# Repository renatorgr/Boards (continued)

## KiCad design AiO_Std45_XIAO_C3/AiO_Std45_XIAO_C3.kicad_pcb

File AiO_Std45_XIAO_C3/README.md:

# XIAO ESP32C3 adapter for the AiO v4.5 Standard (GPS2 socket → Serial2)

A small board (40.0 × 52.6 mm overall, 2 layers, cut away where the Bynav / UM982 module goes) that plugs into the **second GPS socket (GPS2, "F9P RelPosNED")** of the AiO v4.5 Standard, in place of a second simpleRTK2B, and connects a **Seeed XIAO ESP32C3** (or **ESP32S3**) to the **Teensy's Serial2** (pins 7 and 8). The XIAO plugs into two female headers on the adapter.

## Connections

| Socket pin | On the AiO v4.5 Standard | On the adapter |
|---|---|---|
| P8 pin 1 | Teensy pin 7 (RX2) | R1 1 kΩ → D6 (TX) |
| P8 pin 2 | Teensy pin 8 (TX2) | R2 1 kΩ → D7 (RX) |
| P8 pin 3 | pin 1 of H6 (GPS1 socket, dual F9P only) | not connected |
| P7 pin 4 | 5 V (5V1, K7805M 1 A regulator) | D1 (Schottky) → XIAO 5V pin + C1 22 µF |
| P7 pins 2, 3 | GND | GND |
| P7 pin 7 | 3.3 V of the Teensy (IOREF) | **not connected** |
| P7 pins 1, 5, 6, 8 | — | not connected |
| H14 pins 1–6 | — (A0–A5 of the socket, no connections) | not connected: they hold the adapter |

- XIAO ESP32C3: D6 = GPIO21 (TX), D7 = GPIO20 (RX).
- XIAO ESP32S3: D6 = GPIO43 (TX), D7 = GPIO44 (RX).

The positions of the 17 pins were copied from the official AiO v4.5 Standard PCB file (EasyEDA, 2024-02-05) and the nets were checked against its schematic (2024-03-27): 0.000 mm difference.

## Why 5 V and not 3.3 V

- On the Standard, the 3.3 V of the GPS2 socket (P7 pin 7, IOREF) is the Teensy's own 3.3 V output.
- PJRC recommends at most 250 mA from it for external use, and the board already uses it (BNO085, CAN, LEDs, ...). The ESP32's WiFi transmit peaks can go over that.
- The Micro is different: its GPS2 socket has its own 1 A 3.3 V regulator, so the Micro adapter uses 3.3 V.
- This adapter takes the 5 V of the socket (P7 pin 4) through a Schottky diode (D1) into the XIAO's 5V pin, and the XIAO makes its own 3.3 V. Seeed asks for this diode when the 5V pin is fed from outside.
- With D1, the XIAO's USB-C can be plugged in with the adapter on the board: D1 keeps the USB 5 V out of the AiO's 5 V.
- R1 and R2 are 1 kΩ (the Micro adapter too, from its v1.2). If the XIAO is on USB with the AiO switched off, its TX pin feeds the unpowered Teensy through R1; 1 kΩ keeps that current to about 3 mA. At 460800 baud, 1 kΩ makes no difference.

## Shape

- It plugs into P7 (power), P8 pins 1–3 (Serial2) and H14 (6 pins, only to hold it).
- The XIAO sits on the H14 / P8 side of the socket (towards the ADS1115), with its USB-C on the left edge.
- A strip along P7 carries the 5 V. Everything to the right of the XIAO and below that strip is cut away: from 4.0 mm to the right of P7 pin 1 and from 4.6 mm below the P7 row. The Bynav / UM982 module (and the U16 MP1584) can sit under that area.
- A leg goes down to P8 and stays at least 1.5 mm away from the UM982 board drawn on the official PCB (part GPS_UM982EB, socket H20), which covers P8 pins 5–8 and H7.
- P8 and P7 alone would let the adapter go in turned 180°. With H14 it cannot: turned around, its H14 pins land between the holes of H7.
- The outline stays inside the drawing of the GPS2 module on the Standard's silkscreen.

## Files

- `AiO_Std45_XIAO_C3.kicad_pro / .kicad_sch / .kicad_pcb`: KiCad 7 project (schematic + PCB), with its own libraries (`AiO_XIAO_Adapter.pretty`, `AiO_XIAO_Adapter.kicad_sym`).
- `fabrication_JLCPCB/Gerber_AiO_Std45_XIAO_C3.zip`: Gerbers + drill file, ready for JLCPCB.
- `fabrication_JLCPCB/BOM_…csv` and `CPL_…csv`: for JLCPCB's assembly (R1, R2, C1, D1 and the XIAO sockets J4, J5 on the top side, the pin headers J1, J2 and J3 on the bottom side).
- `fabrication_JLCPCB/BOM_…_top_only.csv` and `CPL_…_top_only.csv`: the same without J1, J2 and J3, for an assembly on the top side only.
- `documentation/`: the schematic as a PDF (`adapter_schematic.pdf`), views of the board (`adapter_PCB.png`) and its position on the Standard (`GPS2_socket_view.png`).

## Opening it in EasyEDA

EasyEDA Pro: **File → Import → KiCad**, then choose the project folder (or the .zip). It imports the schematic and the PCB.
EasyEDA is not needed to order the board: the Gerber zip goes straight to JLCPCB.

## Ordering (JLCPCB)

- Gerber: `Gerber_AiO_Std45_XIAO_C3.zip`. 2 layers, 1.6 mm, any colour. The default settings are fine (minimum track 0.3 mm, minimum hole 0.3 mm).
- Assembly: BOM + CPL. JLCPCB solders everything except the XIAO:
  - R1, R2, C1 and D1: SMD parts on the top side;
  - the pin headers J1, J2 and J3: through-hole parts on the **bottom** side, with the long pins pointing down (away from the board). The CPL already gives them on the bottom layer, at the centre of each header;
  - the two female headers J4 and J5 for the XIAO: through-hole parts on the **top** side.
- Through-hole assembly costs a little more than SMD only.
- There are parts on both sides, so choose **Standard PCBA** with assembly on **both sides**. With Economic PCBA or top side only, JLCPCB leaves out J1, J2 and J3 (they are on the bottom) and stops with "Coordinate file missing data for: J1, J2, J3".
- Cheaper alternative: Economic PCBA, top side only, with `BOM_…_top_only.csv` and `CPL_…_top_only.csv` (the same files without J1, J2 and J3), and solder J1, J2 and J3 by hand.
- In JLCPCB's placement preview, check:
  - J1, J2 and J3 on the bottom side, over the rows of holes marked "P8", "P7" and "H14";
  - J4 and J5 on the top side, over the two rows of 7 holes of the XIAO;
  - D1: its band (cathode) on the C1 side, as on the silkscreen.

| Ref. | Part | LCSC |
|---|---|---|
| R1, R2 | 1 kΩ 1 % 0805 | C17513 |
| C1 | 22 µF 0805 X5R 25 V | C45783 |
| D1 | B5819W Schottky 40 V 1 A, SOD-123 | C8598 |
| J1 | 1x03 male header, 2.54 mm, XFCN PZ254V-11-03P | C2937625 |
| J2 | 1x08 male header, 2.54 mm, XFCN PZ254V-11-08P | C492407 |
| J3 | 1x06 male header, 2.54 mm, XFCN PZ254V-11-06P | C492405 |
| J4, J5 | 1x07 female header, 2.54 mm, 8.5 mm high, HCTL PM254-1-07-Z-8.5 | C2897370 |
| U1 | Seeed XIAO ESP32C3 or ESP32S3, plugged into J4 / J5 | (not assembled) |

The headers have 6.1 mm mating pins and a 2.5 mm insulator, like the ones on the AiO board itself. Without assembly, J1, J2 and J3 can be cut from one ordinary 1x40 strip of 2.54 mm male headers.

## Assembly

1. Only if the board did not come assembled: R1, R2, C1 and D1 (D1: the band towards C1), then the headers.
2. **The male headers go underneath**, with the long pins pointing down. When soldering them by hand, to get them well aligned: push them into the Standard's P8, P7 and H14, lay the adapter on top and solder them from above.
   - J1 goes into **P8 pins 1 to 3**: the three holes at the end of P8 closest to the ADS1115 module.
   - J2 goes into P7 (all 8 pins) and J3 into H14 (all 6 pins).
3. **XIAO:** solder the two 1x7 male headers that come with it **underneath the XIAO**, long pins pointing down. To keep them straight, push them into J4 and J5 first, lay the XIAO on top and solder from above.
4. **Plug the XIAO into J4 and J5 with its USB-C at the "USB-C" mark** (left edge, ADS1115 side). The two rows have 7 pins each, so the XIAO also goes in turned 180°: that way the 5 V goes into D6 (a 3.3 V pin) and the XIAO is damaged. Check the USB-C mark before powering the AiO.
5. Orientation of the adapter: the square pads are pin 1, and the silkscreen says "P8", "P7" and "H14" next to the header that goes into each one. The H14 header stops it going in turned around.

## Cautions

- With the adapter in place, the GPS2 socket cannot hold a second F9P (dual F9P).
- The Bynav / UM982 module (H20) and the XIAO can be fitted at the same time. They use different serial ports (the module the GPS1 port, the XIAO Serial2), and both take their 5 V from the 1 A K7805M (5V1).
- Check that the antenna cables of the Bynav / UM982 module do not press on the adapter.
- If there is a standoff in the GPS2 mounting hole next to the ADS1115 (left there for a simpleRTK2B), take it out: it would push on the adapter's leg.
- The XIAO's USB-C can be used with the adapter on the board (see "Why 5 V"): the plug goes in from the left, over the ADS1115 side. The XIAO can also be unplugged to program it, or programmed over WiFi (OTA) after the first time.
- On the sockets the XIAO sits about 11 mm higher than soldered flat (8.5 mm socket + 2.5 mm of the male header). Check that the box lid closes.
- Tractor vibration: hold the XIAO in its sockets, for example with a cable tie around the XIAO and the adapter, or a dot of neutral-cure silicone at the corners (not on the U.FL connector or the buttons).
- In a metal box, use an external WiFi antenna on the XIAO's U.FL connector, taken out through the box.

## Firmware

- Teensy: firmware `v4.5_AiO_WEB`, Serial2 (pins 7 RX2 and 8 TX2) at **460800**. On its web page, Settings → "GPS2 port" must be on automatic (the default): the Teensy finds the XIAO by its hello.
- XIAO: the program `v4.5_XIAO_ESP32` that comes in the firmware zip (already compiled in `v4.5_XIAO_ESP32_bin`, for the C3 and the S3). It uses UART1 on D7 (RX) and D6 (TX) at 460800 and empties the receive FIFO at 64 bytes (`setRxFIFOFull(64)`).
- When it starts, the ESP32 writes a few boot lines at 115200 on D6: the Teensy receives garbage for half a second, and the firmware ignores it.
- The official firmware v26 (Firmware_Teensy_AiO-New-Dawn) uses this same link (Serial2) for its ESP32, also at 460800. See `docs/ESP32_BRIDGE_INTERFACE.md` in that repository.

## Checks done

- The schematic and the PCB have the same connections (netlist exported from the schematic = PCB connections).
- KiCad 7 DRC: 0 errors, 0 warnings, 0 unconnected items.
- The 17 header holes in the drill file match P8 pins 1–3, P7 and H14 of the official AiO v4.5 Standard PCB (AgOpenGPS-Official/Boards): 0.000 mm difference.
- The nets of P8, P7 and H14 checked against the official AiO v4.5 Standard schematic.
- The outline is at least 1.5 mm away from the UM982 board (GPS_UM982EB) drawn on the official PCB, and nothing of the adapter is right of the cut (4.0 mm right of P7 pin 1, 4.6 mm below the P7 row).
- The XIAO sockets J4 and J5 are on the XIAO pin positions of Seeed's official KiCad library (XIAO-ESP32-C3-DIP-SMD): 2 × 7 pins, 2.54 mm, rows 15.24 mm apart.
- J1, J2 and J3 are on the bottom side and J4, J5 on the top side, in the PCB and in the CPL. The holes are the same as in 1.1.
- Not yet made or tested on a real board.

## Versions

- **1.2** (19 Oct 2026): pin headers J1, J2 and J3 with LCSC codes in the BOM and the CPL (bottom side), so JLCPCB solders them too. The XIAO plugs into two 1x7 female headers (J4, J5, top side, also soldered by JLCPCB) instead of being soldered to the board.
- **1.1** (19 Oct 2026): XIAO moved to the H14 / P8 side, USB-C on the left edge; board cut away to the right of the XIAO so the Bynav / UM982 module can be fitted under that area.
- **1.0** (19 Oct 2026): first version (not made).

## Credits

- Design: renatorgr, with Claude (Anthropic), 2026.
- Pin positions and nets: official AiO v4.5 Standard board files (EasyEDA PCB 2024-02-05, schematic 2024-03-27), AgOpenGPS-Official/Boards.
- XIAO pin positions: Seeed Studio OPL KiCad library (XIAO-ESP32-C3-DIP-SMD). 0805 and SOD-123 footprints: KiCad standard library.

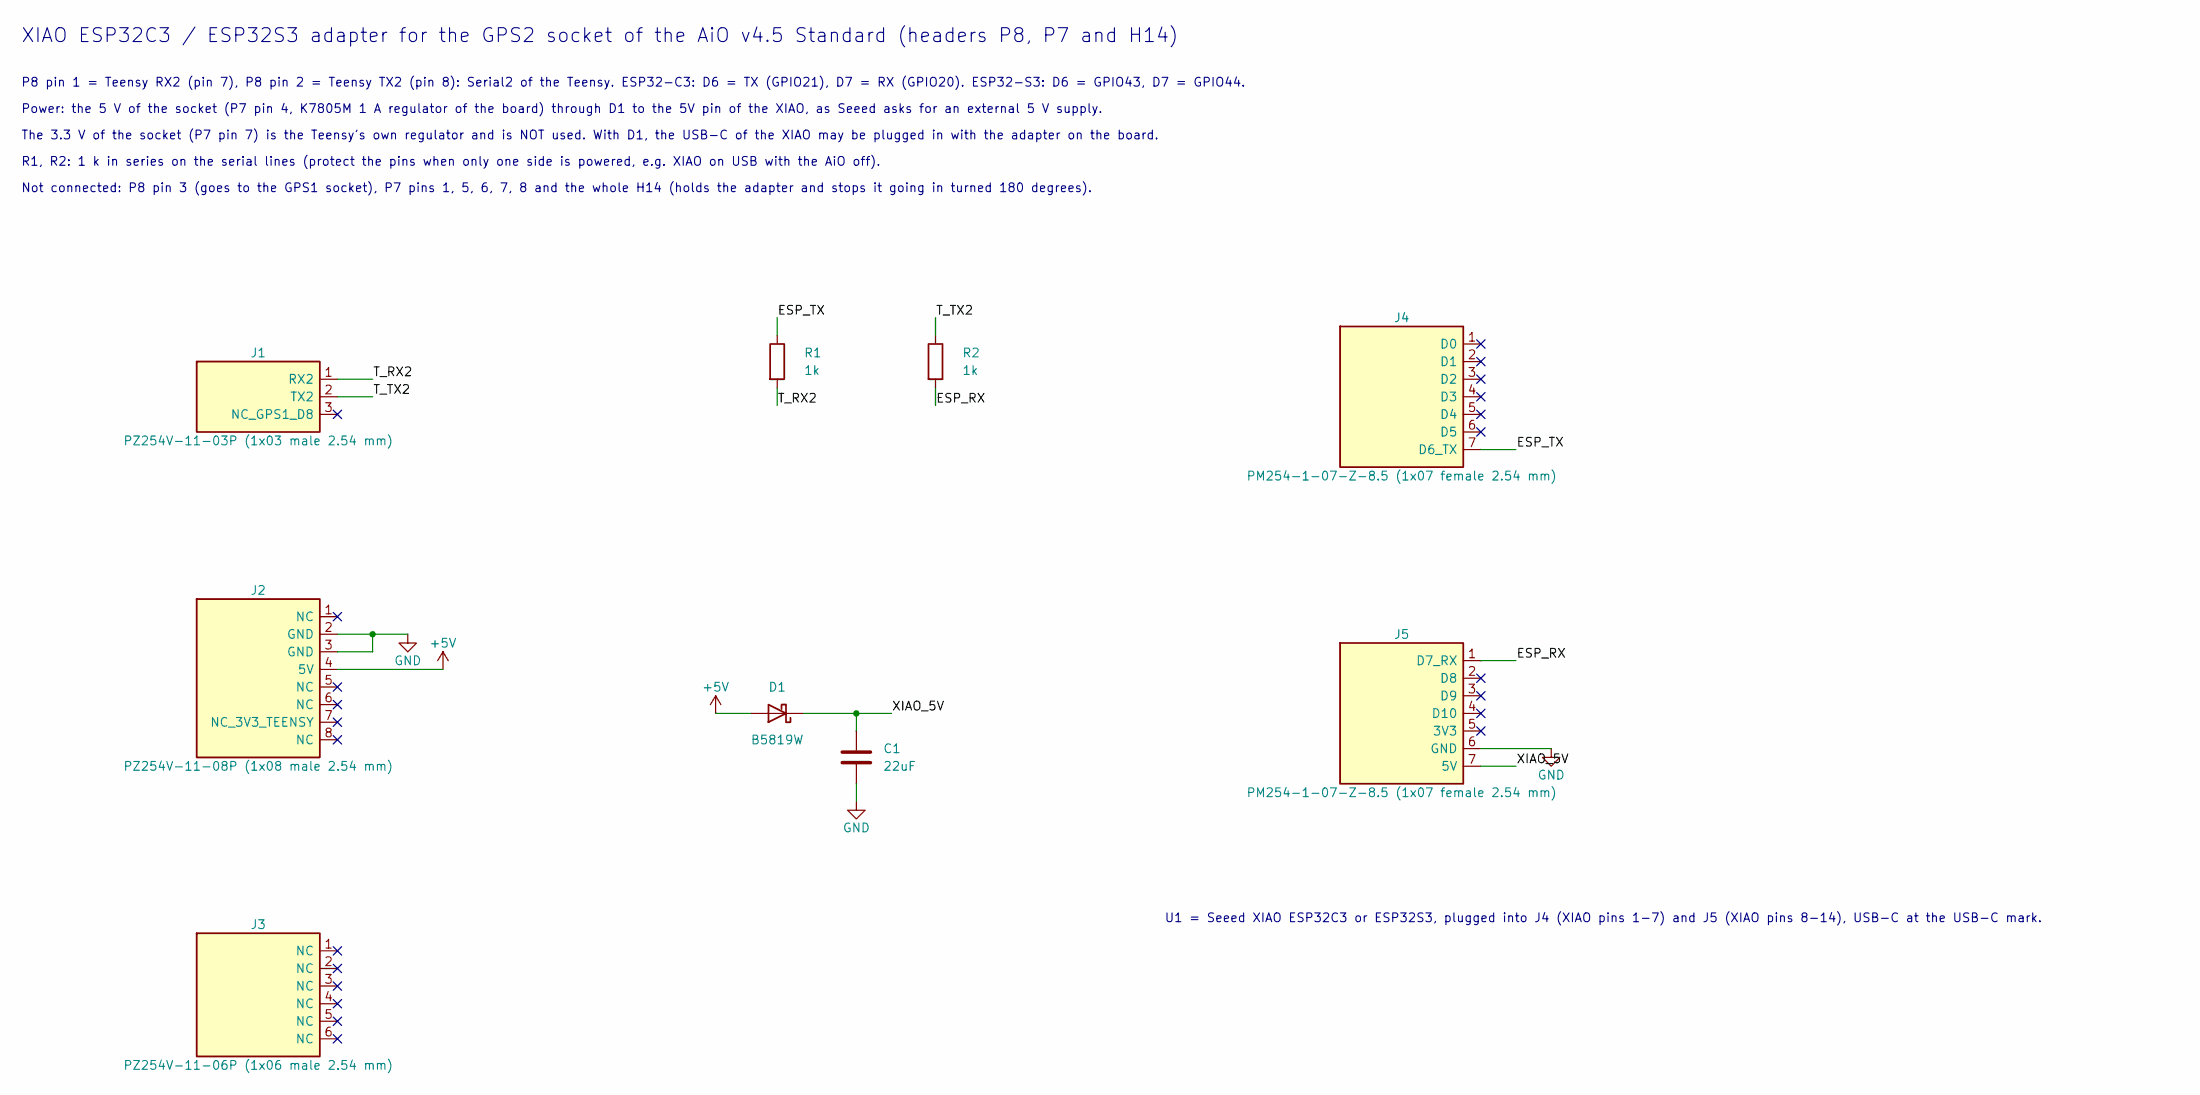
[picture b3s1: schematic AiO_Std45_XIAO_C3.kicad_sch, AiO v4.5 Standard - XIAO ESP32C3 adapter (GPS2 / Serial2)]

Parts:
C1: 22uF; C_0805_2012Metric; LCSC C45783
D1: B5819W; D_SOD-123; LCSC C8598
J1: PZ254V-11-03P (1x03 male 2.54 mm); Plug_1x03_P2.54mm_Bottom; LCSC C2937625
J2: PZ254V-11-08P (1x08 male 2.54 mm); Plug_1x08_P2.54mm_Bottom; LCSC C492407
J3: PZ254V-11-06P (1x06 male 2.54 mm); Plug_1x06_P2.54mm_Bottom; LCSC C492405
J4, J5: PM254-1-07-Z-8.5 (1x07 female 2.54 mm); Socket_1x07_P2.54mm_XIAO; LCSC C2897370
R1, R2: 1k; R_0805_2012Metric; LCSC C17513

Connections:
+5V: D1.2 (A), J2.4 (5V)
/ESP_RX: J5.1 (D7_RX), R2.2
/ESP_TX: J4.7 (D6_TX), R1.1
/T_RX2: J1.1 (RX2), R1.2
/T_TX2: J1.2 (TX2), R2.1
/XIAO_5V: C1.1, D1.1 (K), J5.7 (5V)
GND: C1.2, J2.2 (GND), J2.3 (GND), J5.6 (GND)

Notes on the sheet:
U1 = Seeed XIAO ESP32C3 or ESP32S3, plugged into J4 (XIAO pins 1-7) and J5 (XIAO pins 8-14), USB-C at the USB-C mark.
XIAO ESP32C3 / ESP32S3 adapter for the GPS2 socket of the AiO v4.5 Standard (headers P8, P7 and H14)
P8 pin 1 = Teensy RX2 (pin 7), P8 pin 2 = Teensy TX2 (pin 8): Serial2 of the Teensy. ESP32-C3: D6 = TX (GPIO21), D7 = RX (GPIO20). ESP32-S3: D6 = GPIO43, D7 = GPIO44.
Power: the 5 V of the socket (P7 pin 4, K7805M 1 A regulator of the board) through D1 to the 5V pin of the XIAO, as Seeed asks for an external 5 V supply.
The 3.3 V of the socket (P7 pin 7) is the Teensy's own regulator and is NOT used. With D1, the USB-C of the XIAO may be plugged in with the adapter on the board.
R1, R2: 1 k in series on the serial lines (protect the pins when only one side is powered, e.g. XIAO on USB with the AiO off).
Not connected: P8 pin 3 (goes to the GPS1 socket), P7 pins 1, 5, 6, 7, 8 and the whole H14 (holds the adapter and stops it going in turned 180 degrees).

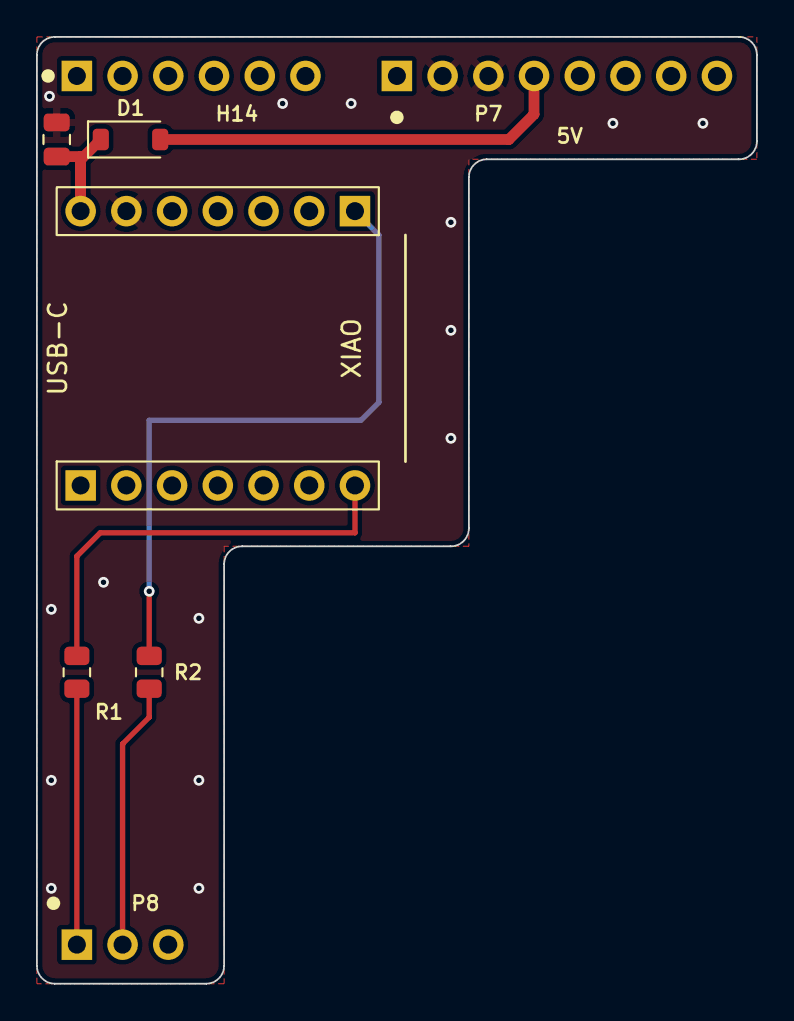
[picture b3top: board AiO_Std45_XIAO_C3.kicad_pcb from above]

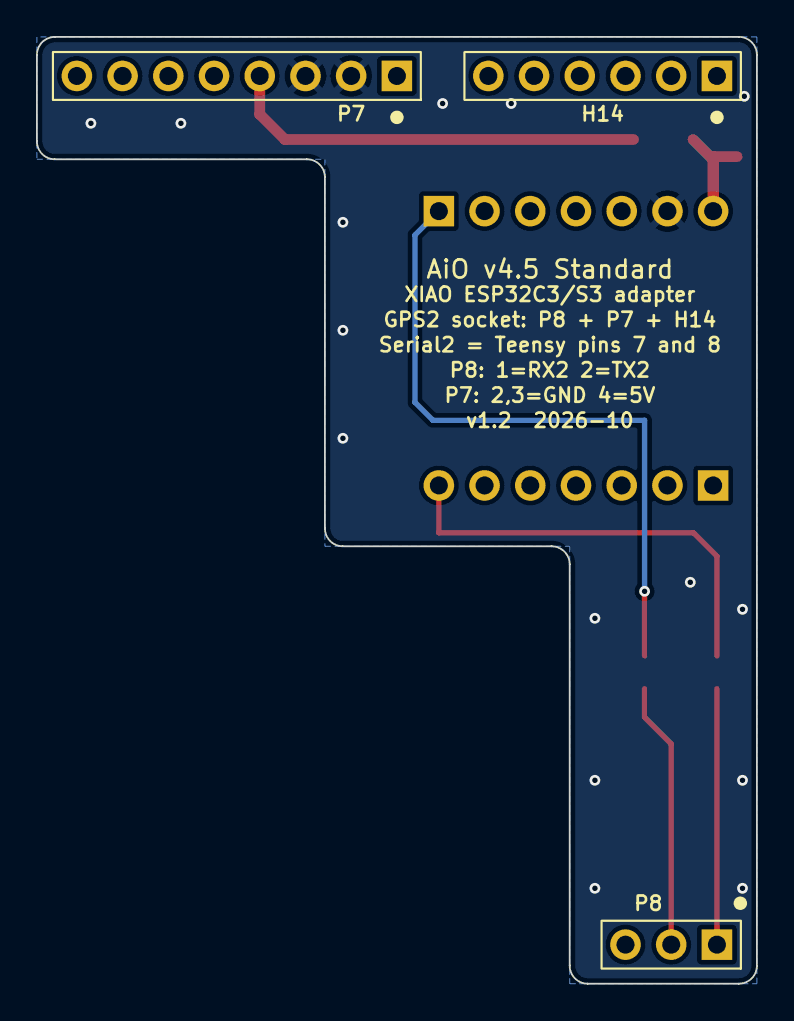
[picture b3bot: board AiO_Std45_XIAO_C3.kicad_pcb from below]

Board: 2 copper layers, 40.0 x 52.6 mm, 9 parts (3 on the bottom side), 7 nets.

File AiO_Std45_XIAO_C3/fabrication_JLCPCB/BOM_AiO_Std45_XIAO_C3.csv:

Comment,Designator,Footprint,LCSC Part #
1k 1% 0805,"R1,R2",R_0805_2012Metric,C17513
22uF 0805 X5R,C1,C_0805_2012Metric,C45783
B5819W Schottky 40V 1A,D1,D_SOD-123,C8598
Pin header 1x03 male 2.54mm PZ254V-11-03P (bottom side),J1,Plug_1x03_P2.54mm_Bottom,C2937625
Pin header 1x08 male 2.54mm PZ254V-11-08P (bottom side),J2,Plug_1x08_P2.54mm_Bottom,C492407
Pin header 1x06 male 2.54mm PZ254V-11-06P (bottom side),J3,Plug_1x06_P2.54mm_Bottom,C492405
Female header 1x07 2.54mm 8.5mm PM254-1-07-Z-8.5 (top side - XIAO socket),"J4,J5",Socket_1x07_P2.54mm_XIAO,C2897370

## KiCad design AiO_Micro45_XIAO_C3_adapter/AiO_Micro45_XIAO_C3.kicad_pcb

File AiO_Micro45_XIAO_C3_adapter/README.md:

# XIAO ESP32C3 adapter for the AiO v4.5 Micro (GPS2 socket → Serial2)

A small board (27.3 × 24.4 mm, 2 layers) that plugs into the **second GPS socket ("Dual-Left", U11)** of the AiO v4.5 Micro, in place of a simpleRTK2B Micro, and connects a **Seeed XIAO ESP32C3** to the **Teensy's Serial2** (pins 7 and 8).

## Connections

| Socket pin | On the AiO v4.5 Micro | On the adapter |
|---|---|---|
| 1 | 3.3 V (1 A K7803M regulator) | XIAO 3V3 + C1 22 µF |
| 2 | Teensy pin 7 (RX2) | R1 100 Ω → D6 (TX, GPIO21) |
| 3 | Teensy pin 8 (TX2) | R2 100 Ω → D7 (RX, GPIO20) |
| 10, 11 | GND | GND |
| 6, 7, 8 | F9P micro-USB | not connected |
| 16 | pin 12 of the GPS1 socket (dual F9P only) | not connected |
| 18 | LED RTK_STAT_1 | not connected |
| others | — | not connected |

The positions of the 20 pins were copied from the official AiO v4.5 Micro PCB file (EasyEDA, 2024-02-05) and checked against the schematic: 0.00 mm difference. The outline stays inside the drawing of the original module on the Micro's silkscreen, with the same cut corner (on the side of LED1 and the RJ45 jack).

## Files

- `AiO_Micro45_XIAO_C3.kicad_pro / .kicad_sch / .kicad_pcb`: KiCad 7 project (schematic + PCB), with its own libraries (`AiO_XIAO_Adapter.pretty`, `AiO_XIAO_Adapter.kicad_sym`).
- `fabrication_JLCPCB/Gerber_AiO_Micro45_XIAO_C3.zip`: Gerbers + drill file, ready for JLCPCB.
- `fabrication_JLCPCB/BOM_…csv` and `CPL_…csv`: for JLCPCB's SMT assembly (R1, R2 and C1 only).
- `documentation/`: the schematic as a PDF (`adapter_schematic.pdf`), views of the board (`adapter_PCB.png`) and its position on the Micro (`GPS2_socket_view.png`).

## Opening it in EasyEDA

EasyEDA Pro: **File → Import → KiCad**, then choose the project folder (or the .zip). It imports the schematic and the PCB.
EasyEDA is not needed to order the board: the Gerber zip goes straight to JLCPCB.

## Ordering (JLCPCB)

- Gerber: `Gerber_AiO_Micro45_XIAO_C3.zip`. 2 layers, 1.6 mm, any colour. The default settings are fine (minimum track 0.3 mm, minimum hole 0.3 mm).
- SMT assembly (optional): BOM + CPL. They are only three 0805 parts and they are easy to solder by hand.

| Ref. | Part | LCSC |
|---|---|---|
| R1, R2 | 100 Ω 1 % 0805 | C17408 |
| C1 | 22 µF 0805 X5R | C45783 |
| J1 | 2 × 1x10 male header, **2.00 mm pitch** | (solder by hand) |
| U1 | Seeed XIAO ESP32C3 | (solder by hand) |

## Assembly

1. R1, R2 and C1 (if they did not come assembled).
2. **The 2.00 mm male headers go underneath**, with the pins pointing down. To get them well aligned: push them into the Micro's GPS2 socket, lay the adapter on top and solder them from above.
3. **XIAO on top**, with the USB-C on the side of the "USB-C" mark:
   - preferably **soldered flat** (by the half-holes on its edge): it sits lower, stands vibration better and leaves no pin ends underneath;
   - if you use the pins that come with the XIAO, **cut the ends flush underneath**. Under the adapter, on the Micro, there is resistor R31, right below the D0–D6 row.
4. Orientation on the Micro: the cut corner of the adapter matches the cut corner drawn on the silkscreen of the GPS2 socket, and pin 1 (square pad, dot on the silkscreen) sits next to pin 1 of the socket.

## Cautions

- The XIAO is powered through its 3V3 pin (the board's 3.3 V). **Do not plug in the XIAO's USB-C with the adapter mounted on the Micro.** Program it off the board, or over WiFi (OTA) after the first time.
- Hammond 1455 boxes are aluminium: use an external WiFi antenna on the XIAO's U.FL connector, taken out through the lid.
- With the adapter in place the GPS2 socket cannot hold a second F9P (dual F9P).

## Firmware

- Teensy: firmware `v4.5_UM982_X20P_F9P_TM171_WEB_XIAO` or `v4.5_AiO_WEB`, Serial2 (pins 7 RX2 and 8 TX2) at **460800**. With `v4.5_AiO_WEB`, the web page setting "GPS2 port" must be on XIAO ESP32 (the default).
- XIAO: the program `v4.5_XIAO_ESP32` that comes in the firmware zip (already compiled in `v4.5_XIAO_ESP32_bin`). It uses UART1 on D7 (RX, GPIO20) and D6 (TX, GPIO21) at 460800 and empties the receive FIFO at 64 bytes (`setRxFIFOFull(64)`).
- The XIAO ESP32S3 fits too: same size and pins (D6 = GPIO43 TX, D7 = GPIO44 RX). The adapter has no copper under its extra pads underneath.
- When it starts, the ESP32-C3 writes a few boot lines at 115200 on GPIO21: the Teensy receives garbage for half a second, and the firmware ignores it.
- The official firmware v26 (Firmware_Teensy_AiO-New-Dawn) uses this same link (Serial2) for its ESP32, also at 460800. See `docs/ESP32_BRIDGE_INTERFACE.md` in that repository.

## Checks done

- The schematic and the PCB have the same connections (netlist exported from the schematic = PCB connections).
- KiCad 7 DRC: 0 errors, 0 unconnected items.
- Pins and connections checked against the official AiO v4.5 Micro schematic and PCB (AgOpenGPS-Official/Boards).
- XIAO footprint as in Seeed's official KiCad library (XIAO-ESP32-C3-DIP-SMD).
- Not yet made or tested on a real board.

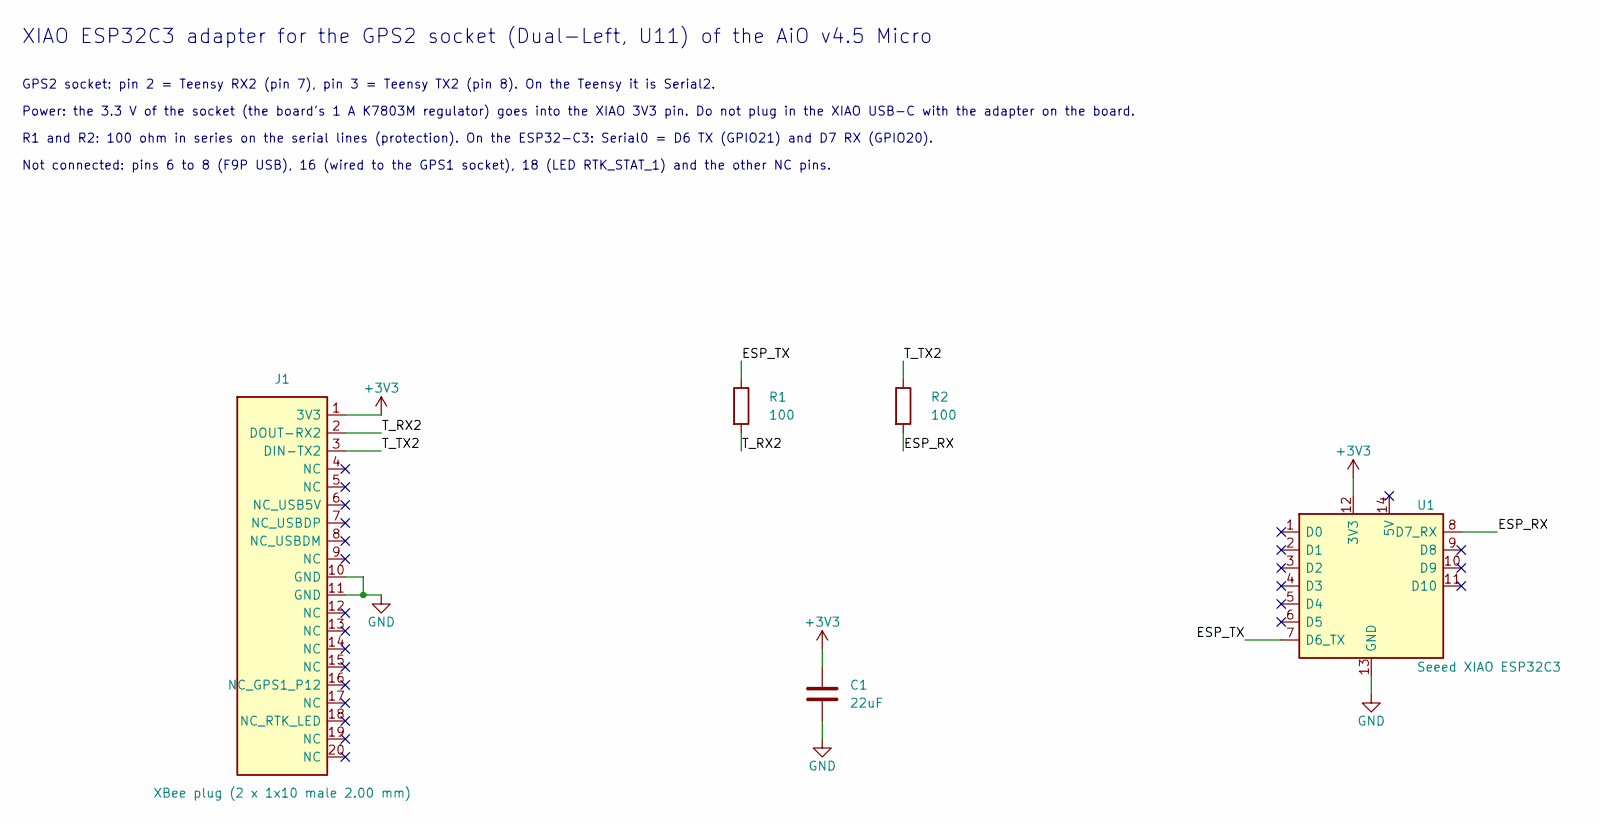
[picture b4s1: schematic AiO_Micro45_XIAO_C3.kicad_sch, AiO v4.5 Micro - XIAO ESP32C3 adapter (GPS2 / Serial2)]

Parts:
C1: 22uF; C_0805_2012Metric; LCSC C45783
J1: XBee plug (2 x 1x10 male 2.00 mm); XBee_Plug_2x10_P2.00mm
R1, R2: 100; R_0805_2012Metric; LCSC C17408
U1: Seeed XIAO ESP32C3; XIAO_ESP32C3_THT_Castellated

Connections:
+3V3: C1.1, J1.1 (3V3), U1.12 (3V3)
/ESP_RX: R2.2, U1.8 (D7_RX)
/ESP_TX: R1.1, U1.7 (D6_TX)
/T_RX2: J1.2 (DOUT-RX2), R1.2
/T_TX2: J1.3 (DIN-TX2), R2.1
GND: C1.2, J1.10 (GND), J1.11 (GND), U1.13 (GND)

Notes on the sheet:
XIAO ESP32C3 adapter for the GPS2 socket (Dual-Left, U11) of the AiO v4.5 Micro
GPS2 socket: pin 2 = Teensy RX2 (pin 7), pin 3 = Teensy TX2 (pin 8). On the Teensy it is Serial2.
Power: the 3.3 V of the socket (the board's 1 A K7803M regulator) goes into the XIAO 3V3 pin. Do not plug in the XIAO USB-C with the adapter on the board.
R1 and R2: 100 ohm in series on the serial lines (protection). On the ESP32-C3: Serial0 = D6 TX (GPIO21) and D7 RX (GPIO20).
Not connected: pins 6 to 8 (F9P USB), 16 (wired to the GPS1 socket), 18 (LED RTK_STAT_1) and the other NC pins.

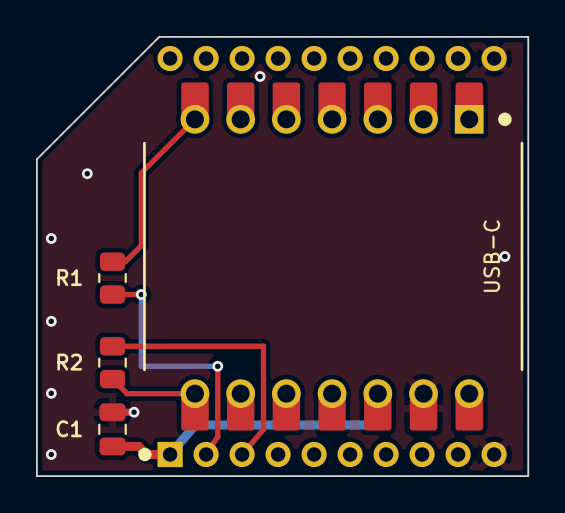
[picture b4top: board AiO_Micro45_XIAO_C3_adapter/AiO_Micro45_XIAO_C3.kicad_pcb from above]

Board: 2 copper layers, 27.3 x 24.4 mm, 5 parts (0 on the bottom side), 6 nets.

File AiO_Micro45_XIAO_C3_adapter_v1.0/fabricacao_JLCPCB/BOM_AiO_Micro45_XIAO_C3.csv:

Comment,Designator,Footprint,LCSC Part #
100R 1% 0805,"R1,R2",R_0805_2012Metric,C17408
22uF 0805 X5R,C1,C_0805_2012Metric,C45783
